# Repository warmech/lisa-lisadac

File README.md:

# LisaDAC
 
This project aims to reproduce Neville & Steele's DAC expansion card for the Apple Lisa (via MacWorks) which provided audio functionality similar to the Macintosh sound hardware. The LisaDAC does not, however, produce 100% compatibility with Mac sound hardware and, as such, has a reduced/degraded audio output when compared to a Macintosh. In some cases, calls made in MacWorks to what would be the Mac's sound hardware when using a LisaDAC may result in MacOS/MacWorks crashing.

## Creator Commentary (10 February, 2025)

Daris A. Nevil, the original creator of this hardware, has generously provided some high-resolution scans and commentary on the history and design of this card. These can be found in the [neville_and_steele](neville_and_steele) directory in the root of this repository. Many thanks to Mr. Nevil for reaching out and providing these! It was a pleasure hearing from you.

## ROM Version

Both version 1.0 (v1_0.BIN) from the Neville & Steele card and 1.1 (v1_1.BIN) from the newer LDAC reproduction are included with this repository. These ROM dumps should be programmed on a 2716 EPROM or other compatible device.

## Jumper Settings

- J3 - Speaker Selection: To use the internal speaker, place a jumper on pins 3 and 4; to use an external speaker, connect the leads to pins 1 and 4.
- J4 - DMA Bus Grant Pass-Through: Whether or not this should have a jumper is debatable; no other Lisa expansion card uses DMA, so there aren't really any other DMA processes to interfere with. The stock configuration is to place a jumper across J4.
- J5 - Unknown: Likely has to do with card slot selection. Configuration "A" jumpers pins 1 and 2 and ties the /SHn (where n is 0, 1, or 2) line on the expansion bus to pin 9 of the 74LS00 at U7; configuration "B" jumpers pins 2 and 3 and ties the +5V rail to pin 9 of the 74LS00 at U7.

## Stability and Crashing

The LisaDAC is generally stable and does not cause stability issues in and of itself when used with a Lisa. Rather, the issue comes with Mac software making unsupported calls to the Mac's (well, MacWorks') sound hardware. StuntCopter, for instance, will run with no issues (albeit not sounding the best) until completing a successful round of five jumps. Upon completion of the fifth successful jump the victory chime is triggered; the call made to play the chime causes MacOS/MacWorks to immediately hang up, requiring either the reset button to be pressed or the Lisa's power to be cycled.

The following is a list of software with known incompatibilities with the LisaDAC:

- StuntCopter
	- Victory ("backflip") chime causes MacOS/MacWorks to crash

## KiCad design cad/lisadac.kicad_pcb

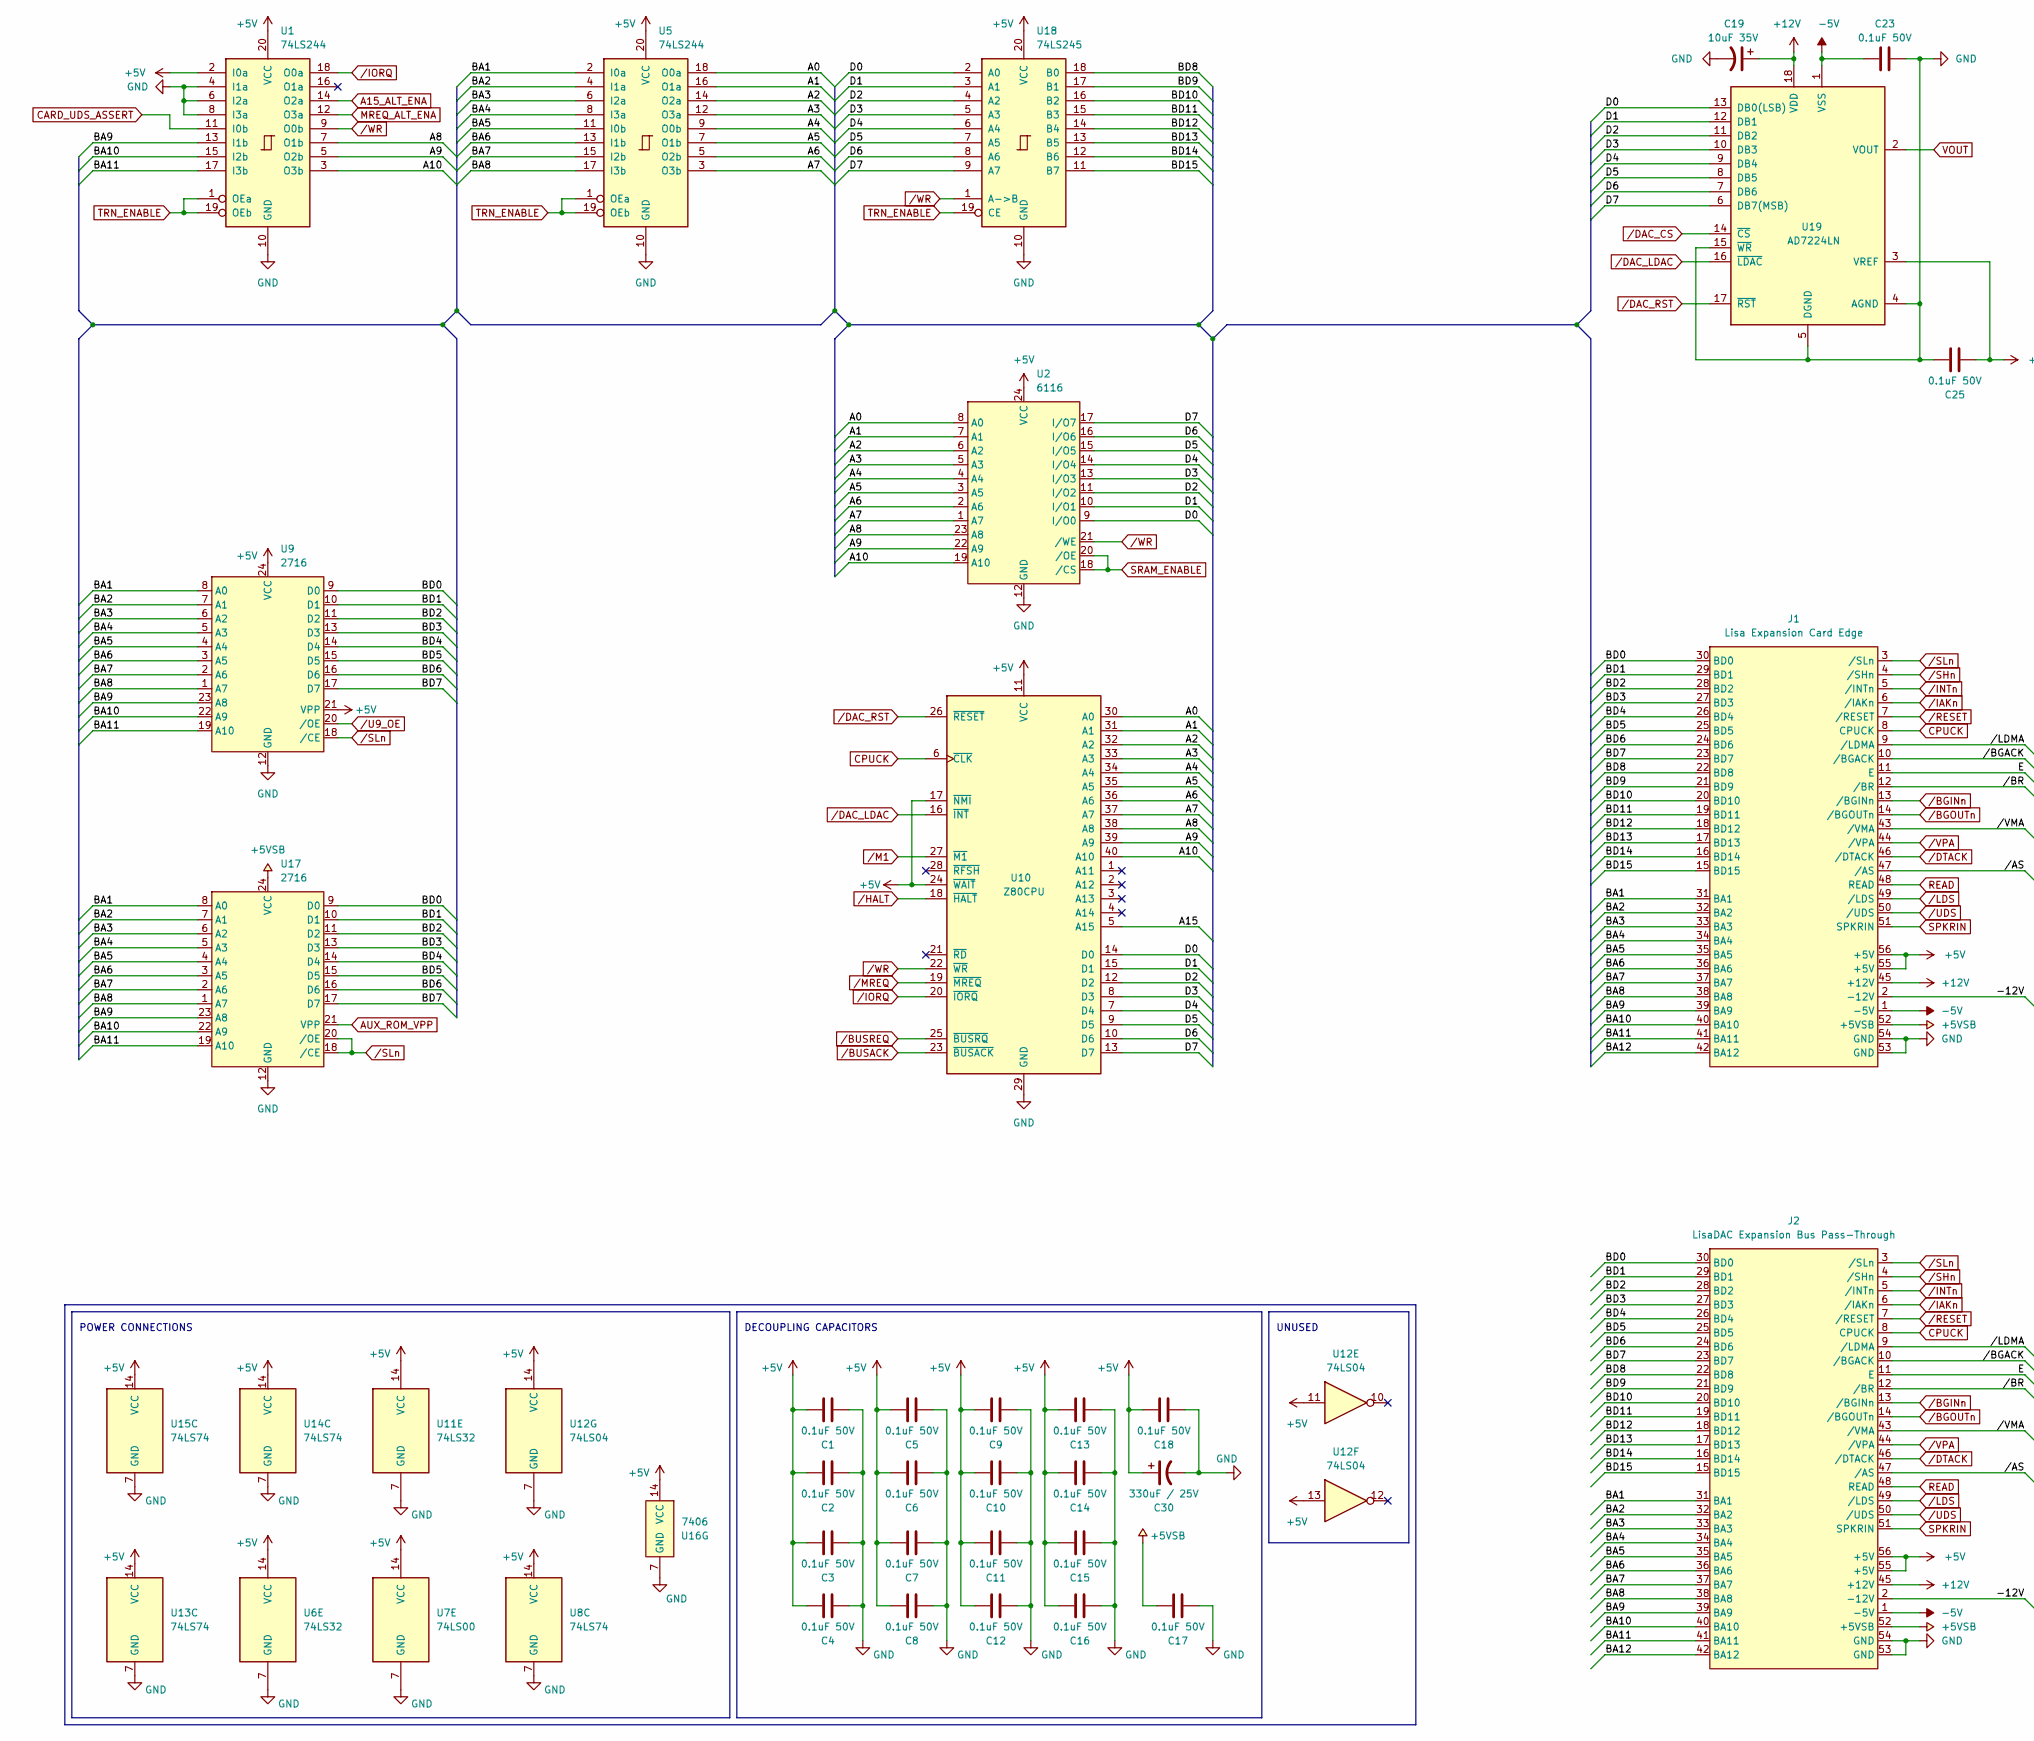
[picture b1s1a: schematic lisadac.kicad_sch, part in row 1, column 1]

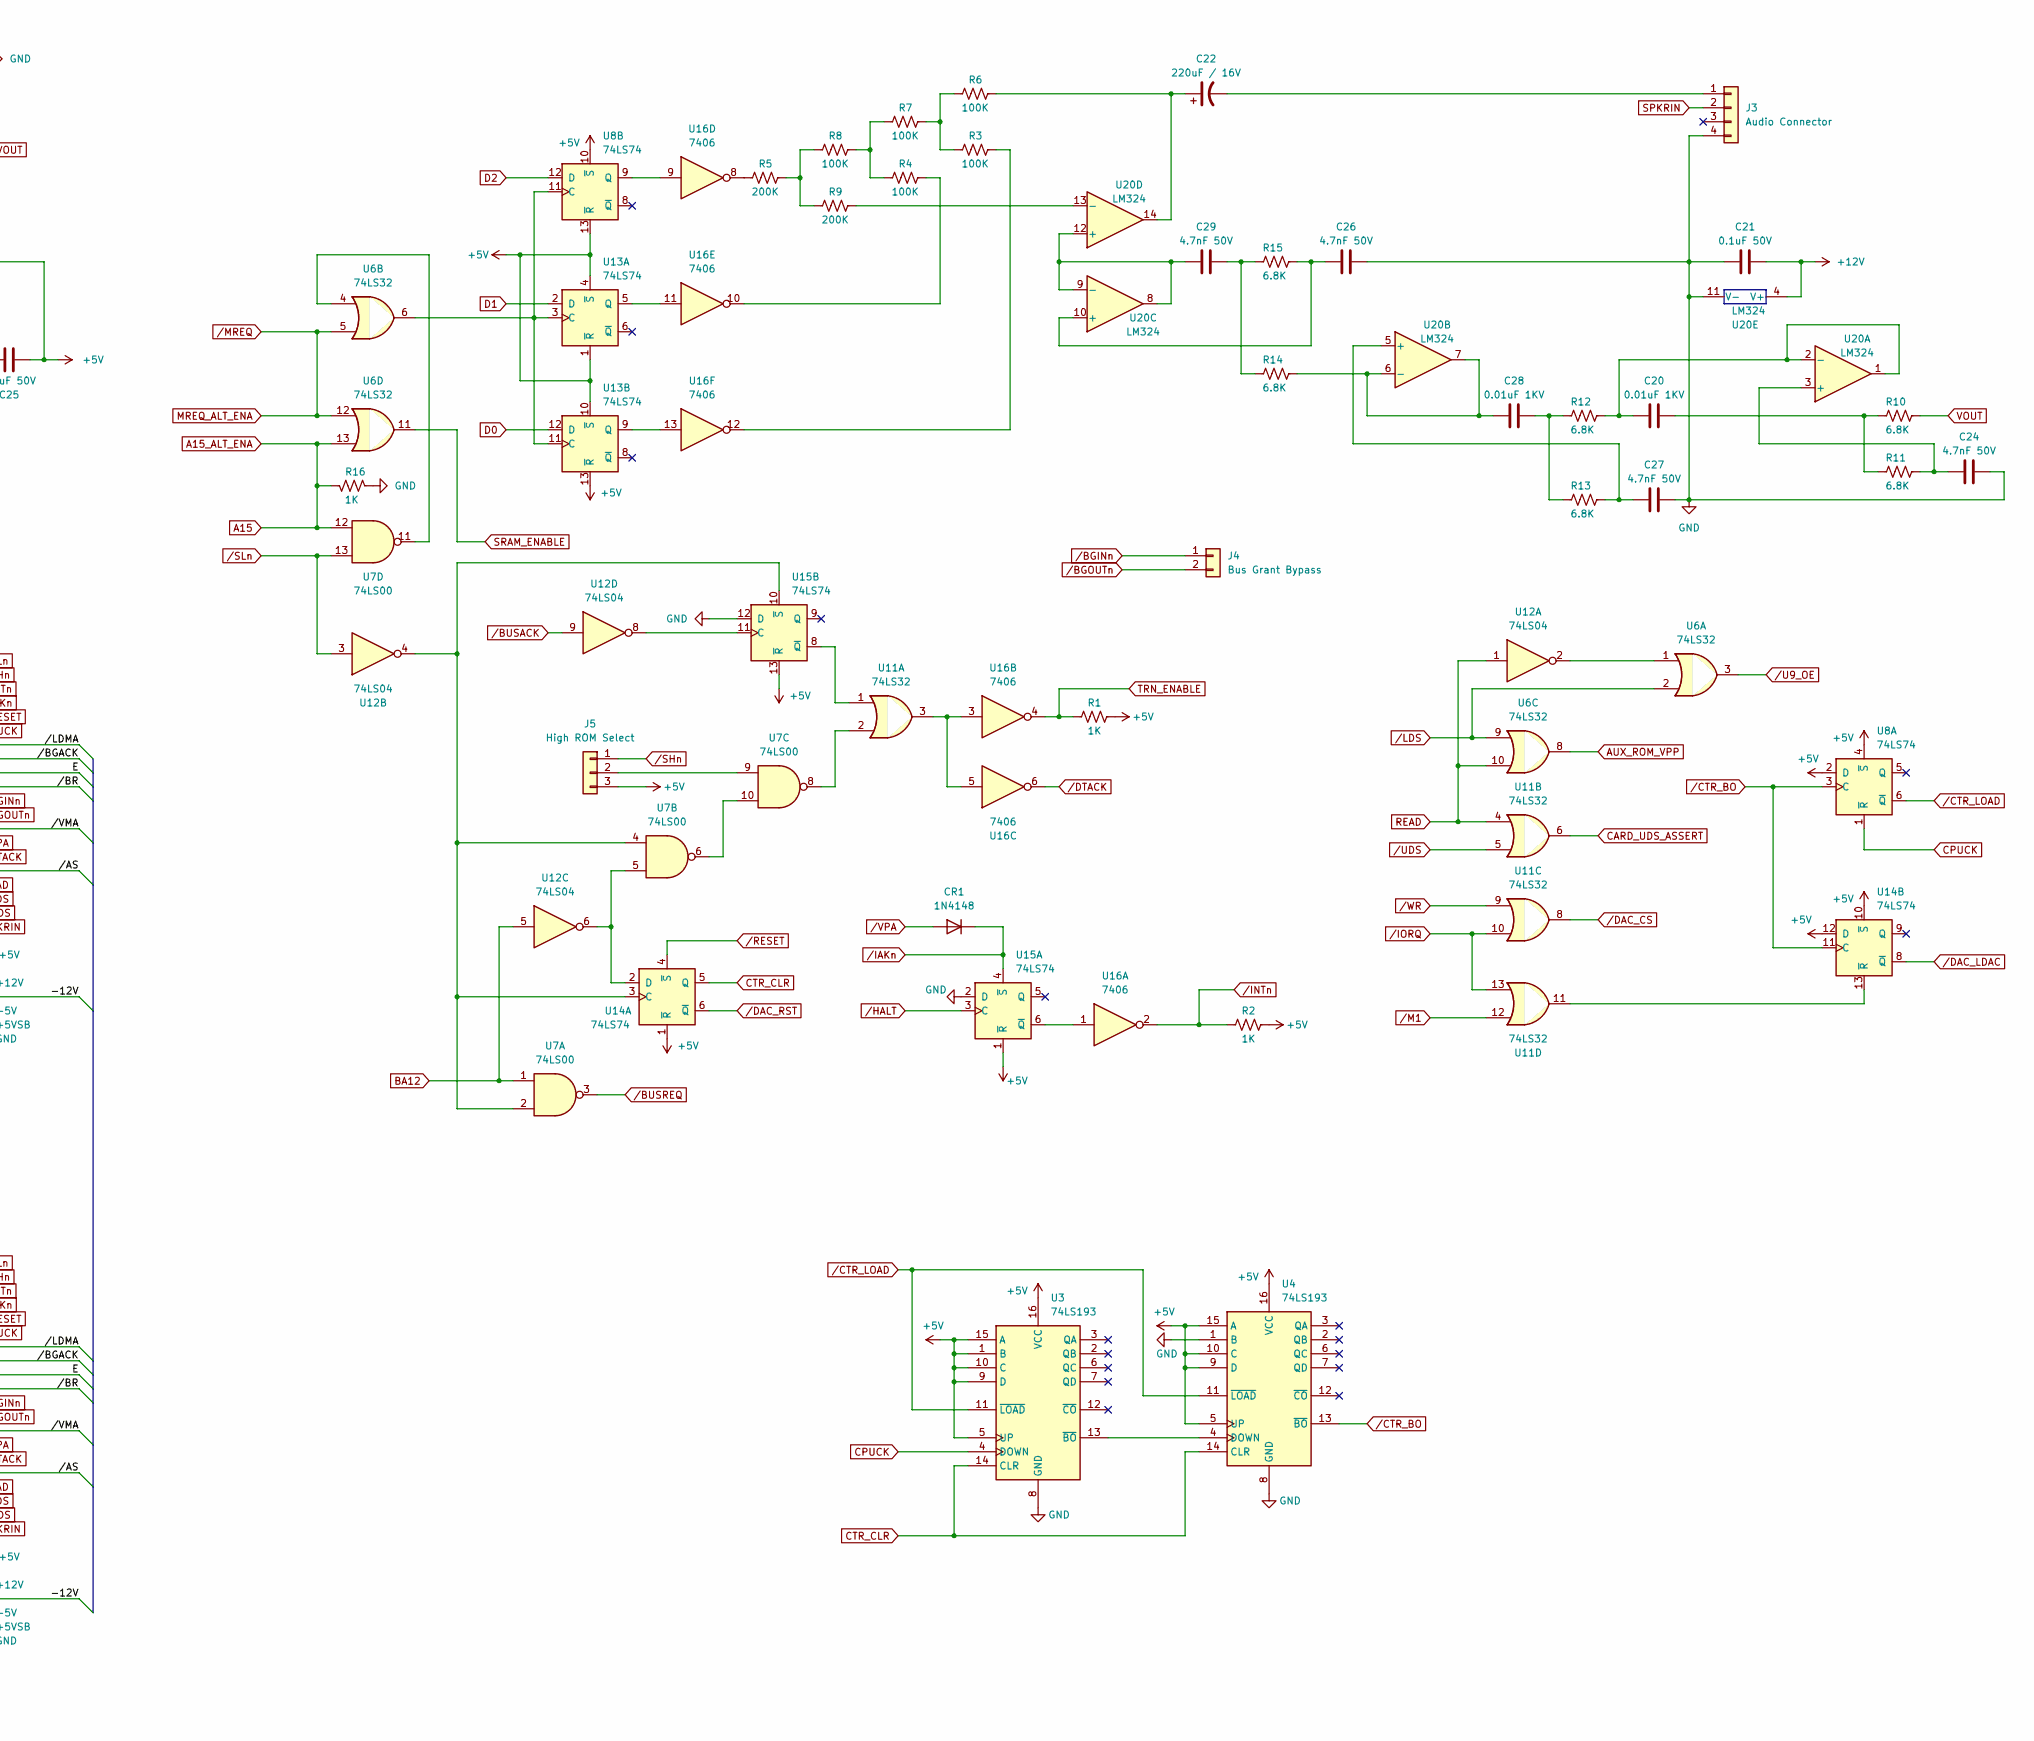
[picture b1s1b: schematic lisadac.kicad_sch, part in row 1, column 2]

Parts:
C1, C2, C3, C4, C5, C6, C7, C8, C9, C10, C11, C12, C13, C14, C15, C16, C17, C18, C21, C23, C25: 0.1uF 50V; C_Disc_D7.0mm_W2.3mm_P5.00mm
C19: 10uF 35V; CP_Radial_D7.8mm_P2.50mm
C20, C28: 0.01uF 1KV; C_Disc_D7.0mm_W2.3mm_P5.00mm
C22: 220uF / 16V; CP_Axial_L21.0mm_D7.6mm_P28.00mm_Horizontal
C24, C26, C27, C29: 4.7nF 50V; C_Disc_D7.0mm_W2.3mm_P5.00mm
C30: 330uF / 25V; C_Disc_D7.0mm_W2.3mm_P5.00mm
CR1: 1N4148; D_DO-35_SOD27_P7.62mm_Horizontal
J1: Lisa Expansion Card Edge; Apple_Lisa_ExpansionBus_CardEdge
J2: LisaDAC Expansion Bus Pass-Through; Apple_Lisa_LisaDAC_ExpansionBus_PassThrough
J3: Audio Connector; PinHeader_1x04_P2.54mm_Vertical
J4: Bus Grant Bypass; PinHeader_1x02_P2.54mm_Vertical
J5: High ROM Select; PinHeader_1x03_P2.54mm_Vertical
R1, R2, R16: 1K; R_Axial_DIN0309_L9.0mm_D2.54mm_P12.70mm_Horizontal
R3, R4, R6, R7, R8: 100K; R_Axial_DIN0309_L9.0mm_D2.54mm_P12.70mm_Horizontal
R5, R9: 200K; R_Axial_DIN0309_L9.0mm_D2.54mm_P12.70mm_Horizontal
R10, R11, R12, R13, R14, R15: 6.8K; R_Axial_DIN0309_L9.0mm_D2.54mm_P12.70mm_Horizontal
U1, U5: 74LS244; DIP-20_W7.62mm
U2: 6116; DIP-24_W15.24mm
U3, U4: 74LS193; DIP-16_W7.62mm
U6, U11: 74LS32; DIP-14_W7.62mm
U7: 74LS00; DIP-14_W7.62mm
U8, U13, U14, U15: 74LS74; DIP-14_W7.62mm
U9, U17: 2716; DIP-24_W15.24mm
U10: Z80CPU; DIP-40_W15.24mm
U12: 74LS04; DIP-14_W7.62mm
U16: 7406; DIP-14_W7.62mm
U18: 74LS245; DIP-20_W7.62mm
U19: AD7224LN; DIP-18_W7.62mm
U20: LM324; DIP-14_W7.62mm

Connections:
+5V: C1.2, C2.2, C3.2, C4.2, C5.2, C6.2, C7.2, C8.2, C9.2, C10.2, C11.2, C12.2, C13.2, C14.2, C15.2, C16.2, C18.2, C25.2, C30.1, J1.55 (+5V), J1.56 (+5V), J2.55 (+5V), J2.56 (+5V), J5.3, R1.1, R2.1, U1.2 (I0a), U1.20 (VCC), U2.24 (VCC), U3.1 (B), U3.5 (UP), U3.9 (D), U3.10 (C), U3.15 (A), U3.16 (VCC), U4.5 (UP), U4.9 (D), U4.10 (C), U4.15 (A), U4.16 (VCC), U5.20 (VCC), U6.14 (VCC), U7.14 (VCC), U8.2 (D), U8.4 (~S), U8.10 (~S), U8.13 (~R), U8.14 (VCC), U9.21 (VPP), U9.24 (VCC), U10.11 (VCC), U10.17 (~NMI), U10.24 (~WAIT), U11.14 (VCC), U12.11, U12.13, U12.14 (VCC), U13.1 (~R), U13.4 (~S), U13.10 (~S), U13.13 (~R), U13.14 (VCC), U14.1 (~R), U14.10 (~S), U14.12 (D), U14.14 (VCC), U15.1 (~R), U15.13 (~R), U15.14 (VCC), U16.14 (VCC), U18.20 (VCC), U19.3 (VREF)
+12V: C19.1, C21.1, J1.45 (+12V), J2.45 (+12V), U19.18 (VDD), U20.4 (V+)
-5V: C23.2, J1.1 (-5V), J2.1 (-5V), U19.1 (VSS)
-15V: C17.2, J1.52 (+5VSB), J2.52 (+5VSB), U17.24 (VCC)
/-12V: J1.2 (-12V), J2.2 (-12V)
/A0: U2.8 (A0), U5.18 (O0a), U10.30 (A0)
/A1: U2.7 (A1), U5.16 (O1a), U10.31 (A1)
/A2: U2.6 (A2), U5.14 (O2a), U10.32 (A2)
/A3: U2.5 (A3), U5.12 (O3a), U10.33 (A3)
/A4: U2.4 (A4), U5.9 (O0b), U10.34 (A4)
/A5: U2.3 (A5), U5.7 (O1b), U10.35 (A5)
/A6: U2.2 (A6), U5.5 (O2b), U10.36 (A6)
/A7: U2.1 (A7), U5.3 (O3b), U10.37 (A7)
/A8: U1.7 (O1b), U2.23 (A8), U10.38 (A8)
/A9: U1.5 (O2b), U2.22 (A9), U10.39 (A9)
/A10: U1.3 (O3b), U2.19 (A10), U10.40 (A10)
/BA1: J1.31 (BA1), J2.31 (BA1), U5.2 (I0a), U9.8 (A0), U17.8 (A0)
/BA2: J1.32 (BA2), J2.32 (BA2), U5.4 (I1a), U9.7 (A1), U17.7 (A1)
/BA3: J1.33 (BA3), J2.33 (BA3), U5.6 (I2a), U9.6 (A2), U17.6 (A2)
/BA4: J1.34 (BA4), J2.34 (BA4), U5.8 (I3a), U9.5 (A3), U17.5 (A3)
/BA5: J1.35 (BA5), J2.35 (BA5), U5.11 (I0b), U9.4 (A4), U17.4 (A4)
/BA6: J1.36 (BA6), J2.36 (BA6), U5.13 (I1b), U9.3 (A5), U17.3 (A5)
/BA7: J1.37 (BA7), J2.37 (BA7), U5.15 (I2b), U9.2 (A6), U17.2 (A6)
/BA8: J1.38 (BA8), J2.38 (BA8), U5.17 (I3b), U9.1 (A7), U17.1 (A7)
/BA9: J1.39 (BA9), J2.39 (BA9), U1.13 (I1b), U9.23 (A8), U17.23 (A8)
/BA10: J1.40 (BA10), J2.40 (BA10), U1.15 (I2b), U9.22 (A9), U17.22 (A9)
/BA11: J1.41 (BA11), J2.41 (BA11), U1.17 (I3b), U9.19 (A10), U17.19 (A10)
/BD0: J1.30 (BD0), J2.30 (BD0), U9.9 (D0), U17.9 (D0)
/BD1: J1.29 (BD1), J2.29 (BD1), U9.10 (D1), U17.10 (D1)
/BD2: J1.28 (BD2), J2.28 (BD2), U9.11 (D2), U17.11 (D2)
/BD3: J1.27 (BD3), J2.27 (BD3), U9.13 (D3), U17.13 (D3)
/BD4: J1.26 (BD4), J2.26 (BD4), U9.14 (D4), U17.14 (D4)
/BD5: J1.25 (BD5), J2.25 (BD5), U9.15 (D5), U17.15 (D5)
/BD6: J1.24 (BD6), J2.24 (BD6), U9.16 (D6), U17.16 (D6)
/BD7: J1.23 (BD7), J2.23 (BD7), U9.17 (D7), U17.17 (D7)
/BD8: J1.22 (BD8), J2.22 (BD8), U18.18 (B0)
/BD9: J1.21 (BD9), J2.21 (BD9), U18.17 (B1)
/BD10: J1.20 (BD10), J2.20 (BD10), U18.16 (B2)
/BD11: J1.19 (BD11), J2.19 (BD11), U18.15 (B3)
/BD12: J1.18 (BD12), J2.18 (BD12), U18.14 (B4)
/BD13: J1.17 (BD13), J2.17 (BD13), U18.13 (B5)
/BD14: J1.16 (BD14), J2.16 (BD14), U18.12 (B6)
/BD15: J1.15 (BD15), J2.15 (BD15), U18.11 (B7)
/D3: U2.13 (I/O3), U10.8 (D3), U18.5 (A3), U19.10 (DB3)
/D4: U2.14 (I/O4), U10.7 (D4), U18.6 (A4), U19.9 (DB4)
/D5: U2.15 (I/O5), U10.9 (D5), U18.7 (A5), U19.8 (DB5)
/D6: U2.16 (I/O6), U10.10 (D6), U18.8 (A6), U19.7 (DB6)
/D7: U2.17 (I/O7), U10.13 (D7), U18.9 (A7), U19.6 (DB7(MSB))
/E: J1.11 (E), J2.11 (E)
//AS: J1.47 (/AS), J2.47 (/AS)
//BGACK: J1.10 (/BGACK), J2.10 (/BGACK)
//BR: J1.12 (/BR), J2.12 (/BR)
//LDMA: J1.9 (/LDMA), J2.9 (/LDMA)
//VMA: J1.43 (/VMA), J2.43 (/VMA)
A15: R16.1, U1.14 (O2a), U6.13, U7.12, U10.5 (A15)
AUX_ROM_VPP: U6.8, U17.21 (VPP)
BA12: J1.42 (BA12), J2.42 (BA12), U7.1, U12.5
CARD_UDS_ASSERT: U1.11 (I0b), U11.6
CPUCK: J1.8 (CPUCK), J2.8 (CPUCK), U3.4 (DOWN), U8.1 (~R), U10.6 (~CLK)
CTR_CLR: U3.14 (CLR), U4.14 (CLR), U14.5 (Q)
D0: U2.9 (I/O0), U10.14 (D0), U13.12 (D), U18.2 (A0), U19.13 (DB0(LSB))
D1: U2.10 (I/O1), U10.15 (D1), U13.2 (D), U18.3 (A1), U19.12 (DB1)
D2: U2.11 (I/O2), U8.12 (D), U10.12 (D2), U18.4 (A2), U19.11 (DB2)
GND: C1.1, C2.1, C3.1, C4.1, C5.1, C6.1, C7.1, C8.1, C9.1, C10.1, C11.1, C12.1, C13.1, C14.1, C15.1, C16.1, C17.1, C18.1, C19.2, C21.2, C23.1, C24.2, C25.1, C26.2, C27.1, C30.2, J1.53 (GND), J1.54 (GND), J2.53 (GND), J2.54 (GND), J3.4, R16.2, U1.4 (I1a), U1.6 (I2a), U1.8 (I3a), U1.10 (GND), U2.12 (GND), U3.8 (GND), U4.1 (B), U4.8 (GND), U5.10 (GND), U6.7 (GND), U7.7 (GND), U8.7 (GND), U9.12 (GND), U10.29 (GND), U11.7 (GND), U12.7 (GND), U13.7 (GND), U14.7 (GND), U15.2 (D), U15.7 (GND), U15.12 (D), U16.7 (GND), U17.12 (GND), U18.10 (GND), U19.4 (AGND), U19.5 (DGND), U19.15 (~WR), U20.11 (V-)
MREQ_ALT_ENA: U1.12 (O3a), U6.5, U6.12, U10.19 (~MREQ)
unnamed: C20.2, R10.2, R11.2
unnamed: C22.1, R6.1, U20.14
unnamed: C28.2, R12.2, R13.2
unnamed: C29.2, R14.2, R15.2
unnamed: C22.2, J3.1
unnamed: J5.2, U7.9
unnamed: R3.1, U16.12
unnamed: R3.2, R6.2, R7.1
unnamed: R4.1, U16.10
unnamed: R4.2, R7.2, R8.1
unnamed: R5.1, R8.2, R9.2
unnamed: R5.2, U16.8
unnamed: U3.13 (~BO), U4.4 (DOWN)
unnamed: U6.4, U7.11
unnamed: U7.6, U7.10
unnamed: U8.9 (Q), U16.9
unnamed: U7.8, U11.2
unnamed: U11.3, U16.3, U16.5
unnamed: U6.1, U12.2
unnamed: U6.6, U8.11 (C), U13.3 (C), U13.11 (C)
unnamed: U13.5 (Q), U16.11
unnamed: U13.9 (Q), U16.13
unnamed: U7.2, U7.4, U12.4, U14.3 (C), U15.10 (~S)
unnamed: U7.5, U12.6, U14.2 (D)
unnamed: U11.11, U14.13 (~R)
unnamed: U15.6 (~Q), U16.1
unnamed: U12.8, U15.11 (C)
unnamed: U11.1, U15.8 (~Q)
unnamed: C24.1, R11.1, U20.3 (+)
unnamed: C20.1, R12.1, U20.1, U20.2 (-)
unnamed: C27.2, R13.1, U20.5 (+)
unnamed: C28.1, R14.1, U20.6 (-), U20.7
unnamed: C26.1, R15.1, U20.10 (+)
unnamed: C29.1, U20.8, U20.9 (-), U20.12 (+)
unnamed: R9.1, U20.13 (-)
READ: J1.48 (READ), J2.48 (READ), U6.10, U11.4, U12.1
SPKRIN: J1.51 (SPKRIN), J2.51 (SPKRIN), J3.2
SRAM_ENABLE: U2.18 (/CS), U2.20 (/OE), U6.11
TRN_ENABLE: R1.2, U1.1 (OEa), U1.19 (OEb), U5.1 (OEa), U5.19 (OEb), U16.4, U18.19 (CE)
VOUT: R10.1, U19.2 (VOUT)
/BGINn: J1.13 (/BGINn), J2.13 (/BGINn), J4.1
/BGOUTn: J1.14 (/BGOUTn), J2.14 (/BGOUTn), J4.2
/BUSACK: U10.23 (~BUSACK), U12.9
/BUSREQ: U7.3, U10.25 (~BUSRQ)
/CTR_BO: U4.13 (~BO), U8.3 (C), U14.11 (C)
/CTR_LOAD: U3.11 (~LOAD), U4.11 (~LOAD), U8.6 (~Q)
/DAC_CS: U11.8, U19.14 (~CS)
/DAC_LDAC: U10.16 (~INT), U14.8 (~Q), U19.16 (~LDAC)
/DAC_RST: U10.26 (~RESET), U14.6 (~Q), U19.17 (~RST)
/DTACK: J1.46 (/DTACK), J2.46 (/DTACK), U16.6
/HALT: U10.18 (~HALT), U15.3 (C)
/IAKn: CR1.1 (K), J1.6 (/IAKn), J2.6 (/IAKn), U15.4 (~S)
/INTn: J1.5 (/INTn), J2.5 (/INTn), R2.2, U16.2
/IORQ: U1.18 (O0a), U10.20 (~IORQ), U11.10, U11.13
/LDS: J1.49 (/LDS), J2.49 (/LDS), U6.2, U6.9
/M1: U10.27 (~M1), U11.12
/RESET: J1.7 (/RESET), J2.7 (/RESET), U14.4 (~S)
/SHn: J1.4 (/SHn), J2.4 (/SHn), J5.1
/SLn: J1.3 (/SLn), J2.3 (/SLn), U7.13, U9.18 (/CE), U12.3, U17.18 (/CE), U17.20 (/OE)
/U9_OE: U6.3, U9.20 (/OE)
/UDS: J1.50 (/UDS), J2.50 (/UDS), U11.5
/VPA: CR1.2 (A), J1.44 (/VPA), J2.44 (/VPA)
/WR: U1.9 (O0b), U2.21 (/WE), U10.22 (~WR), U11.9, U18.1 (A->B)

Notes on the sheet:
POWER CONNECTIONS
UNUSED
DECOUPLING CAPACITORS

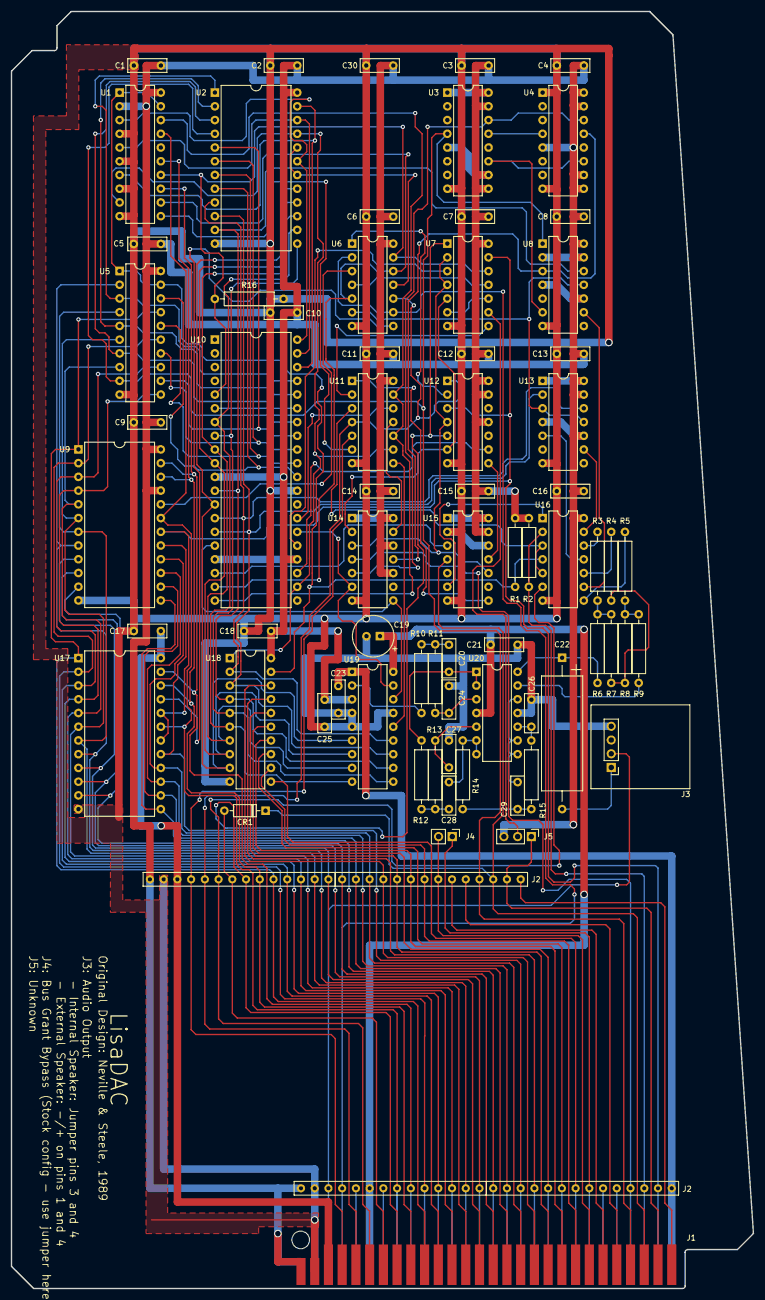
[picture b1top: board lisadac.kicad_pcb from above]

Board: 2 copper layers, 137.2 x 236.2 mm, 72 parts (0 on the bottom side), 128 nets.

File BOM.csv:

"#","Reference","Qty","Value","Footprint","DNP"
"1","C1, C2, C3, C4, C5, C6, C7, C8, C9, C10, C11, C12, C13, C14, C15, C16, C17, C18, C21, C23, C25","21","0.1uF 50V","Capacitor_THT_Custom:C_Disc_D7.0mm_W2.3mm_P5.00mm",""
"2","C19","1","10uF 35V","Capacitor_THT_Custom:CP_Radial_D7.8mm_P2.50mm",""
"3","C20, C28","2","0.01uF 1KV","Capacitor_THT_Custom:C_Disc_D7.0mm_W2.3mm_P5.00mm",""
"4","C22","1","220uF / 16V","Capacitor_THT_Custom:CP_Axial_L21.0mm_D7.6mm_P28.00mm_Horizontal",""
"5","C24, C26, C27, C29","4","4.7nF 50V","Capacitor_THT_Custom:C_Disc_D7.0mm_W2.3mm_P5.00mm",""
"6","C30","1","330uF / 25V","Capacitor_THT_Custom:C_Disc_D7.0mm_W2.3mm_P5.00mm",""
"7","CR1","1","1N4148","Diode_THT:D_DO-35_SOD27_P7.62mm_Horizontal",""
"8","J3","1","Audio Connector","Connector_PinHeader_2.54mm:PinHeader_1x04_P2.54mm_Vertical",""
"9","J4","1","Bus Grant Bypass","Connector_PinHeader_2.54mm:PinHeader_1x02_P2.54mm_Vertical",""
"10","J5","1","High ROM Select","Connector_PinHeader_2.54mm:PinHeader_1x03_P2.54mm_Vertical",""
"11","R1, R2, R16","3","1K","Resistor_THT_Custom:R_Axial_DIN0309_L9.0mm_D2.54mm_P12.70mm_Horizontal",""
"12","R3, R4, R6, R7, R8","5","100K","Resistor_THT_Custom:R_Axial_DIN0309_L9.0mm_D2.54mm_P12.70mm_Horizontal",""
"13","R5, R9","2","200K","Resistor_THT_Custom:R_Axial_DIN0309_L9.0mm_D2.54mm_P12.70mm_Horizontal",""
"14","R10, R11, R12, R13, R14, R15","6","6.8K","Resistor_THT_Custom:R_Axial_DIN0309_L9.0mm_D2.54mm_P12.70mm_Horizontal",""
"15","U1, U5","2","74LS244","Package_DIP:DIP-20_W7.62mm",""
"16","U2","1","6116","Package_DIP:DIP-24_W15.24mm",""
"17","U3, U4","2","74LS193","Package_DIP:DIP-16_W7.62mm",""
"18","U6, U11","2","74LS32","Package_DIP:DIP-14_W7.62mm",""
"19","U7","1","74LS00","Package_DIP:DIP-14_W7.62mm",""
"20","U8, U13, U14, U15","4","74LS74","Package_DIP:DIP-14_W7.62mm",""
"21","U9, U17","2","2716","Package_DIP:DIP-24_W15.24mm",""
"22","U10","1","Z80CPU","Package_DIP:DIP-40_W15.24mm",""
"23","U12","1","74LS04","Package_DIP:DIP-14_W7.62mm",""
"24","U16","1","7406","Package_DIP:DIP-14_W7.62mm",""
"25","U18","1","74LS245","Package_DIP:DIP-20_W7.62mm",""
"26","U19","1","AD7224LN","Package_DIP:DIP-18_W7.62mm",""
"27","U20","1","LM324","Package_DIP:DIP-14_W7.62mm",""

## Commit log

2024-02-25 Release commit
2025-02-10 Added a little historic background.
2025-10-20 Removed junk metadata files from project
